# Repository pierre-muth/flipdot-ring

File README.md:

# flipdot-ring
Files of the flipdot-ring project
It's basically a big circular flipdot display acting as a clock.

Details on www.pierremuth.com

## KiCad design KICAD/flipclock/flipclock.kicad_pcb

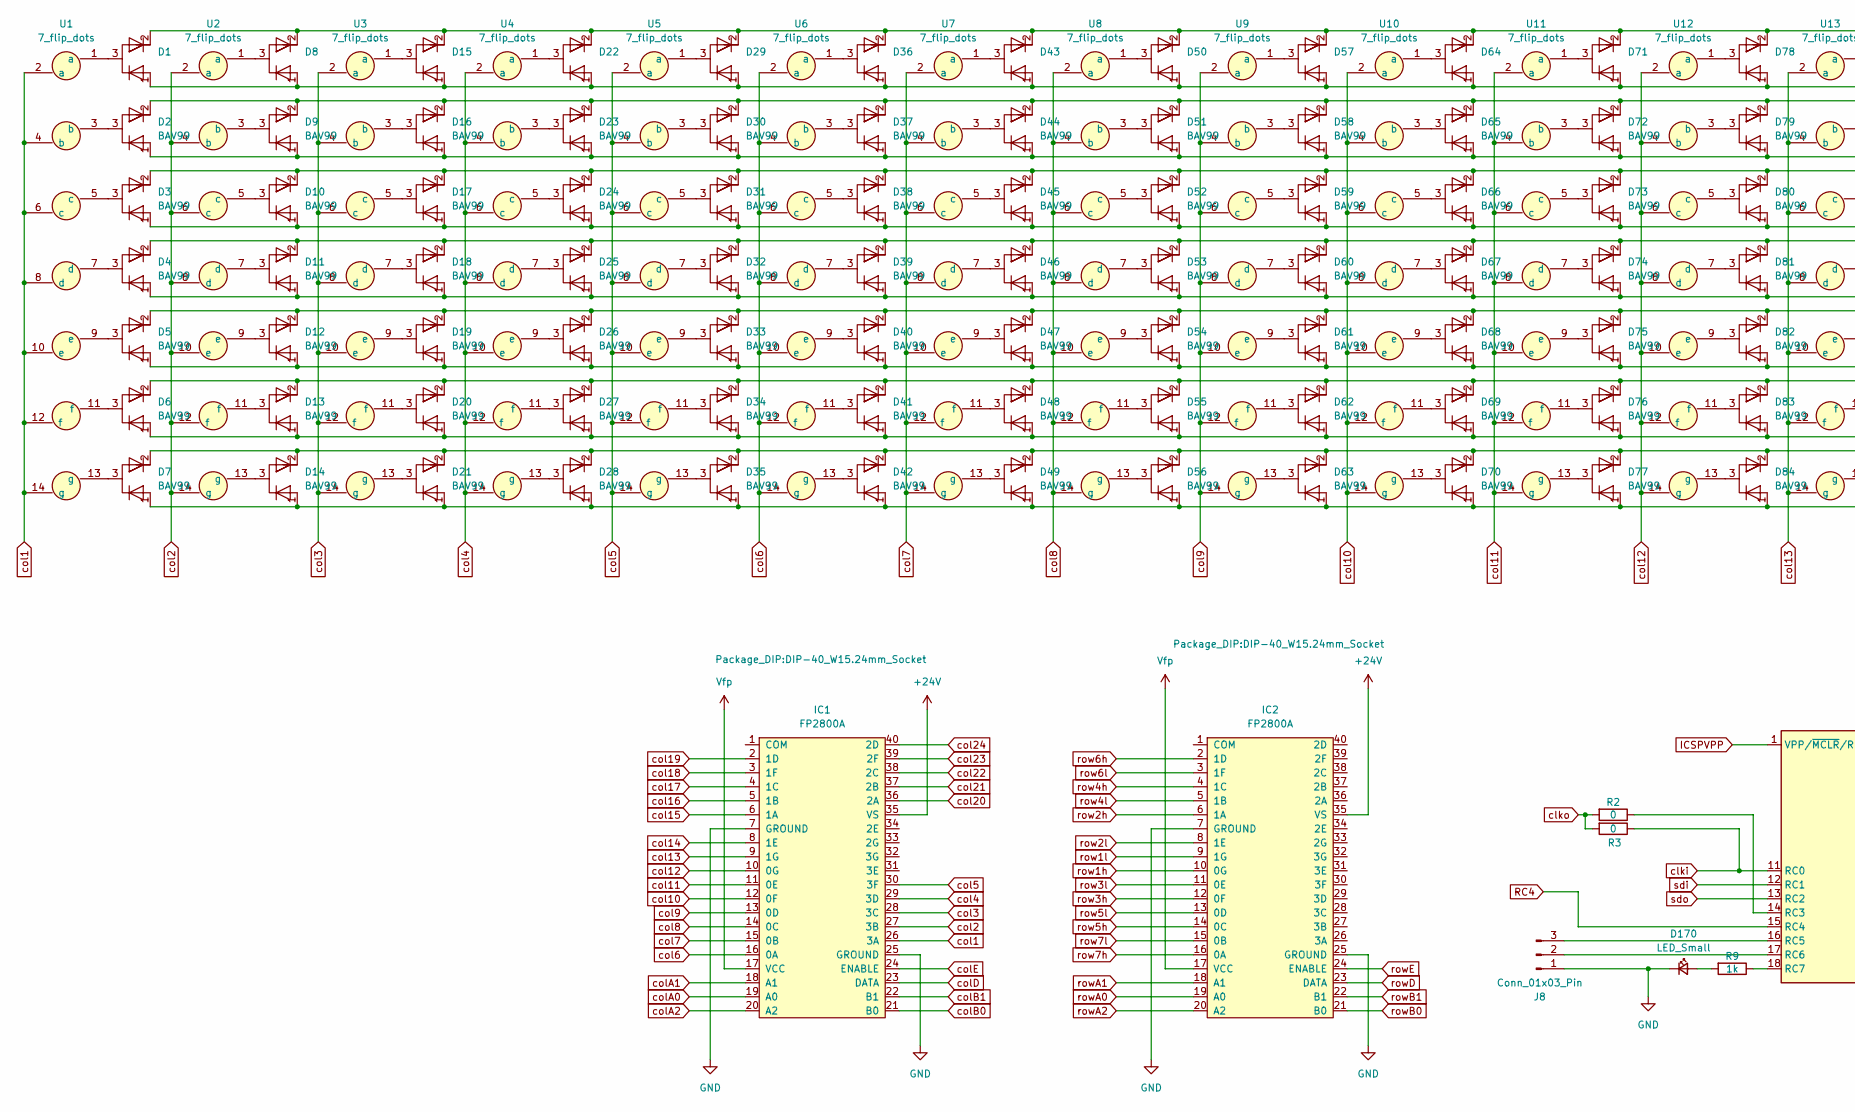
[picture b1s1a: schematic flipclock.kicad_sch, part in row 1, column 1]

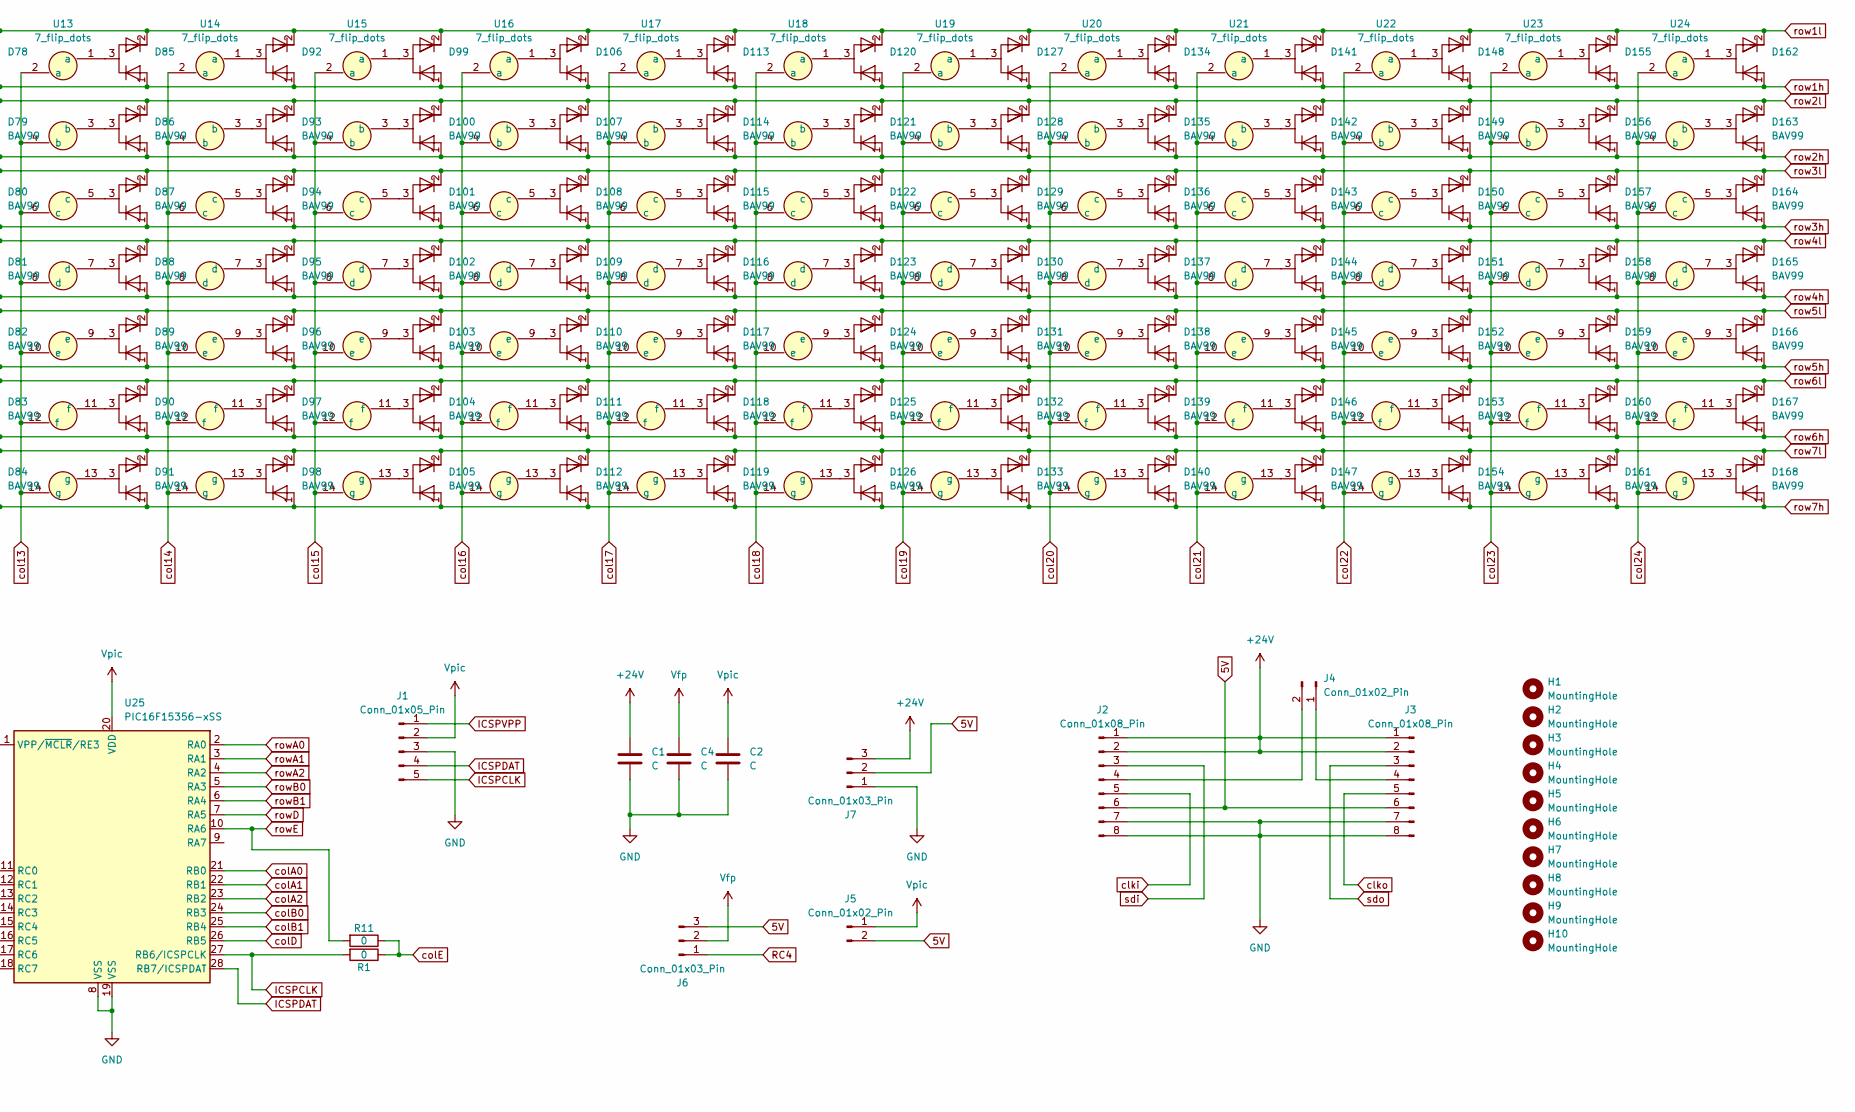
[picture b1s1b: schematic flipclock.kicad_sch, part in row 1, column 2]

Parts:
C1, C2, C4: C; C_1210_3225Metric_Pad1.33x2.70mm_HandSolder
D1, D2, D3, D4, D5, D6, D7, D8, D9, D10, D11, D12, D13, D14, D15, D16, D17, D18, D19, D20, D21, D22, D23, D24, D25, D26, D27, D28, D29, D30, D31, D32, D33, D34, D35, D36, D37, D38, D39, D40, D41, D42, D43, D44, D45, D46, D47, D48, D49, D50, D51, D52, D53, D54, D55, D56, D57, D58, D59, D60, D61, D62, D63, D64, D65, D66, D67, D68, D69, D70, D71, D72, D73, D74, D75, D76, D77, D78, D79, D80, D81, D82, D83, D84, D85, D86, D87, D88, D89, D90, D91, D92, D93, D94, D95, D96, D97, D98, D99, D100, D101, D102, D103, D104, D105, D106, D107, D108, D109, D110, D111, D112, D113, D114, D115, D116, D117, D118, D119, D120, D121, D122, D123, D124, D125, D126, D127, D128, D129, D130, D131, D132, D133, D134, D135, D136, D137, D138, D139, D140, D141, D142, D143, D144, D145, D146, D147, D148, D149, D150, D151, D152, D153, D154, D155, D156, D157, D158, D159, D160, D161, D162, D163, D164, D165, D166, D167, D168: BAV99; SOT-23
D170: LED_Small; LED_0805_2012Metric
H1, H2, H3, H4, H5, H6, H7, H8, H9, H10: MountingHole; MountingHole_3.2mm_M3
IC1, IC2: FP2800A; DIP-40_W15.24mm_Socket
J1: Conn_01x05_Pin; PinHeader_1x05_P2.54mm_Vertical
J2, J3: Conn_01x08_Pin; PinHeader_2x04_P2.54mm_Vertical
J4, J5: Conn_01x02_Pin; PinHeader_1x02_P2.54mm_Vertical
J6, J7, J8: Conn_01x03_Pin; PinHeader_1x03_P2.54mm_Vertical
R1, R2, R3, R11: 0; R_0805_2012Metric
R9: 1k; R_0805_2012Metric
U1, U2, U3, U4, U5, U6, U7, U8, U9, U10, U11, U12, U13, U14, U15, U16, U17, U18, U19, U20, U21, U22, U23, U24: 7_flip_dots; 7x1flipdot
U25: PIC16F15356-xSS; SSOP-28_5.3x10.2mm_P0.65mm

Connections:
5V: J2.6, J3.6, J5.2, J6.3, J7.2
+24V: C1.2, IC1.35 (VS), IC2.35 (VS), J2.1, J2.2, J3.1, J3.2, J7.3
GND: C1.1, C2.1, C4.1, D170.1 (K), IC1.7 (GROUND), IC1.25 (GROUND), IC2.7 (GROUND), IC2.25 (GROUND), J1.3, J2.7, J2.8, J3.7, J3.8, J7.1, J8.1, U25.8 (VSS), U25.19 (VSS)
ICSPCLK: J1.5, R1.2, U25.27 (RB6/ICSPCLK)
ICSPDAT: J1.4, U25.28 (RB7/ICSPDAT)
ICSPVPP: J1.1, U25.1 (VPP/~MCLR/RE3)
unnamed: D1.3 (K), U1.1 (a)
unnamed: D2.3 (K), U1.3 (b)
unnamed: D3.3 (K), U1.5 (c)
unnamed: D4.3 (K), U1.7 (d)
unnamed: D5.3 (K), U1.9 (e)
unnamed: D6.3 (K), U1.11 (f)
unnamed: D7.3 (K), U1.13 (g)
unnamed: D8.3 (K), U2.1 (a)
unnamed: D9.3 (K), U2.3 (b)
unnamed: D10.3 (K), U2.5 (c)
unnamed: D11.3 (K), U2.7 (d)
unnamed: D12.3 (K), U2.9 (e)
unnamed: D13.3 (K), U2.11 (f)
unnamed: D14.3 (K), U2.13 (g)
unnamed: D15.3 (K), U3.1 (a)
unnamed: D16.3 (K), U3.3 (b)
unnamed: D17.3 (K), U3.5 (c)
unnamed: D18.3 (K), U3.7 (d)
unnamed: D19.3 (K), U3.9 (e)
unnamed: D20.3 (K), U3.11 (f)
unnamed: D21.3 (K), U3.13 (g)
unnamed: D22.3 (K), U4.1 (a)
unnamed: D23.3 (K), U4.3 (b)
unnamed: D24.3 (K), U4.5 (c)
unnamed: D25.3 (K), U4.7 (d)
unnamed: D26.3 (K), U4.9 (e)
unnamed: D27.3 (K), U4.11 (f)
unnamed: D28.3 (K), U4.13 (g)
unnamed: D29.3 (K), U5.1 (a)
unnamed: D30.3 (K), U5.3 (b)
unnamed: D31.3 (K), U5.5 (c)
unnamed: D32.3 (K), U5.7 (d)
unnamed: D33.3 (K), U5.9 (e)
unnamed: D34.3 (K), U5.11 (f)
unnamed: D35.3 (K), U5.13 (g)
unnamed: D36.3 (K), U6.1 (a)
unnamed: D37.3 (K), U6.3 (b)
unnamed: D38.3 (K), U6.5 (c)
unnamed: D39.3 (K), U6.7 (d)
unnamed: D40.3 (K), U6.9 (e)
unnamed: D41.3 (K), U6.11 (f)
unnamed: D42.3 (K), U6.13 (g)
unnamed: D43.3 (K), U7.1 (a)
unnamed: D44.3 (K), U7.3 (b)
unnamed: D45.3 (K), U7.5 (c)
unnamed: D46.3 (K), U7.7 (d)
unnamed: D47.3 (K), U7.9 (e)
unnamed: D48.3 (K), U7.11 (f)
unnamed: D49.3 (K), U7.13 (g)
unnamed: D50.3 (K), U8.1 (a)
unnamed: D51.3 (K), U8.3 (b)
unnamed: D52.3 (K), U8.5 (c)
unnamed: D53.3 (K), U8.7 (d)
unnamed: D54.3 (K), U8.9 (e)
unnamed: D55.3 (K), U8.11 (f)
unnamed: D56.3 (K), U8.13 (g)
unnamed: D57.3 (K), U9.1 (a)
unnamed: D58.3 (K), U9.3 (b)
unnamed: D59.3 (K), U9.5 (c)
unnamed: D60.3 (K), U9.7 (d)
unnamed: D61.3 (K), U9.9 (e)
unnamed: D62.3 (K), U9.11 (f)
unnamed: D63.3 (K), U9.13 (g)
unnamed: D64.3 (K), U10.1 (a)
unnamed: D65.3 (K), U10.3 (b)
unnamed: D66.3 (K), U10.5 (c)
unnamed: D67.3 (K), U10.7 (d)
unnamed: D68.3 (K), U10.9 (e)
unnamed: D69.3 (K), U10.11 (f)
unnamed: D70.3 (K), U10.13 (g)
unnamed: D71.3 (K), U11.1 (a)
unnamed: D72.3 (K), U11.3 (b)
unnamed: D73.3 (K), U11.5 (c)
unnamed: D74.3 (K), U11.7 (d)
unnamed: D75.3 (K), U11.9 (e)
unnamed: D76.3 (K), U11.11 (f)
unnamed: D77.3 (K), U11.13 (g)
unnamed: D78.3 (K), U12.1 (a)
unnamed: D79.3 (K), U12.3 (b)
unnamed: D80.3 (K), U12.5 (c)
unnamed: D81.3 (K), U12.7 (d)
unnamed: D82.3 (K), U12.9 (e)
unnamed: D83.3 (K), U12.11 (f)
unnamed: D84.3 (K), U12.13 (g)
unnamed: D85.3 (K), U13.1 (a)
unnamed: D86.3 (K), U13.3 (b)
unnamed: D87.3 (K), U13.5 (c)
unnamed: D88.3 (K), U13.7 (d)
unnamed: D89.3 (K), U13.9 (e)
unnamed: D90.3 (K), U13.11 (f)
unnamed: D91.3 (K), U13.13 (g)
unnamed: D92.3 (K), U14.1 (a)
unnamed: D93.3 (K), U14.3 (b)
unnamed: D94.3 (K), U14.5 (c)
unnamed: D95.3 (K), U14.7 (d)
unnamed: D96.3 (K), U14.9 (e)
unnamed: D97.3 (K), U14.11 (f)
unnamed: D98.3 (K), U14.13 (g)
unnamed: D99.3 (K), U15.1 (a)
unnamed: D100.3 (K), U15.3 (b)
unnamed: D101.3 (K), U15.5 (c)
unnamed: D102.3 (K), U15.7 (d)
unnamed: D103.3 (K), U15.9 (e)
unnamed: D104.3 (K), U15.11 (f)
unnamed: D105.3 (K), U15.13 (g)
unnamed: D106.3 (K), U16.1 (a)
unnamed: D107.3 (K), U16.3 (b)
unnamed: D108.3 (K), U16.5 (c)
unnamed: D109.3 (K), U16.7 (d)
unnamed: D110.3 (K), U16.9 (e)
unnamed: D111.3 (K), U16.11 (f)
unnamed: D112.3 (K), U16.13 (g)
unnamed: D113.3 (K), U17.1 (a)
unnamed: D114.3 (K), U17.3 (b)
unnamed: D115.3 (K), U17.5 (c)
unnamed: D116.3 (K), U17.7 (d)
unnamed: D117.3 (K), U17.9 (e)
unnamed: D118.3 (K), U17.11 (f)
unnamed: D119.3 (K), U17.13 (g)
unnamed: D120.3 (K), U18.1 (a)
unnamed: D121.3 (K), U18.3 (b)
unnamed: D122.3 (K), U18.5 (c)
unnamed: D123.3 (K), U18.7 (d)
unnamed: D124.3 (K), U18.9 (e)
unnamed: D125.3 (K), U18.11 (f)
unnamed: D126.3 (K), U18.13 (g)
unnamed: D127.3 (K), U19.1 (a)
unnamed: D128.3 (K), U19.3 (b)
unnamed: D129.3 (K), U19.5 (c)
unnamed: D130.3 (K), U19.7 (d)
unnamed: D131.3 (K), U19.9 (e)
unnamed: D132.3 (K), U19.11 (f)
unnamed: D133.3 (K), U19.13 (g)
unnamed: D134.3 (K), U20.1 (a)
unnamed: D135.3 (K), U20.3 (b)
unnamed: D136.3 (K), U20.5 (c)
unnamed: D137.3 (K), U20.7 (d)
unnamed: D138.3 (K), U20.9 (e)
unnamed: D139.3 (K), U20.11 (f)
unnamed: D140.3 (K), U20.13 (g)
unnamed: D141.3 (K), U21.1 (a)
unnamed: D142.3 (K), U21.3 (b)
unnamed: D143.3 (K), U21.5 (c)
unnamed: D144.3 (K), U21.7 (d)
unnamed: D145.3 (K), U21.9 (e)
unnamed: D146.3 (K), U21.11 (f)
unnamed: D147.3 (K), U21.13 (g)
unnamed: D148.3 (K), U22.1 (a)
unnamed: D149.3 (K), U22.3 (b)
unnamed: D150.3 (K), U22.5 (c)
unnamed: D151.3 (K), U22.7 (d)
unnamed: D152.3 (K), U22.9 (e)
unnamed: D153.3 (K), U22.11 (f)
unnamed: D154.3 (K), U22.13 (g)
unnamed: D155.3 (K), U23.1 (a)
unnamed: D156.3 (K), U23.3 (b)
unnamed: D157.3 (K), U23.5 (c)
unnamed: D158.3 (K), U23.7 (d)
unnamed: D159.3 (K), U23.9 (e)
unnamed: D160.3 (K), U23.11 (f)
unnamed: D161.3 (K), U23.13 (g)
unnamed: D162.3 (K), U24.1 (a)
unnamed: D163.3 (K), U24.3 (b)
unnamed: D164.3 (K), U24.5 (c)
unnamed: D165.3 (K), U24.7 (d)
unnamed: D166.3 (K), U24.9 (e)
unnamed: D167.3 (K), U24.11 (f)
unnamed: D168.3 (K), U24.13 (g)
unnamed: D170.2 (A), R9.2
unnamed: J2.4, J4.2
unnamed: J3.4, J4.1
unnamed: J8.2, U25.17 (RC6)
unnamed: J8.3, U25.16 (RC5)
unnamed: R2.1, U25.14 (RC3)
unnamed: R9.1, U25.18 (RC7)
RC4: J6.1, U25.15 (RC4)
Vfp: C4.2, IC1.17 (VCC), IC2.17 (VCC), J6.2
Vpic: C2.2, J1.2, J5.1, U25.20 (VDD)
clki: J2.5, R3.1, U25.11 (RC0)
clko: J3.5, R2.2, R3.2
col1: IC1.26 (3A), U1.2 (a), U1.4 (b), U1.6 (c), U1.8 (d), U1.10 (e), U1.12 (f), U1.14 (g)
col2: IC1.27 (3B), U2.2 (a), U2.4 (b), U2.6 (c), U2.8 (d), U2.10 (e), U2.12 (f), U2.14 (g)
col3: IC1.28 (3C), U3.2 (a), U3.4 (b), U3.6 (c), U3.8 (d), U3.10 (e), U3.12 (f), U3.14 (g)
col4: IC1.29 (3D), U4.2 (a), U4.4 (b), U4.6 (c), U4.8 (d), U4.10 (e), U4.12 (f), U4.14 (g)
col5: IC1.30 (3F), U5.2 (a), U5.4 (b), U5.6 (c), U5.8 (d), U5.10 (e), U5.12 (f), U5.14 (g)
col6: IC1.16 (0A), U6.2 (a), U6.4 (b), U6.6 (c), U6.8 (d), U6.10 (e), U6.12 (f), U6.14 (g)
col7: IC1.15 (0B), U7.2 (a), U7.4 (b), U7.6 (c), U7.8 (d), U7.10 (e), U7.12 (f), U7.14 (g)
col8: IC1.14 (0C), U8.2 (a), U8.4 (b), U8.6 (c), U8.8 (d), U8.10 (e), U8.12 (f), U8.14 (g)
col9: IC1.13 (0D), U9.2 (a), U9.4 (b), U9.6 (c), U9.8 (d), U9.10 (e), U9.12 (f), U9.14 (g)
col10: IC1.12 (0F), U10.2 (a), U10.4 (b), U10.6 (c), U10.8 (d), U10.10 (e), U10.12 (f), U10.14 (g)
col11: IC1.11 (0E), U11.2 (a), U11.4 (b), U11.6 (c), U11.8 (d), U11.10 (e), U11.12 (f), U11.14 (g)
col12: IC1.10 (0G), U12.2 (a), U12.4 (b), U12.6 (c), U12.8 (d), U12.10 (e), U12.12 (f), U12.14 (g)
col13: IC1.9 (1G), U13.2 (a), U13.4 (b), U13.6 (c), U13.8 (d), U13.10 (e), U13.12 (f), U13.14 (g)
col14: IC1.8 (1E), U14.2 (a), U14.4 (b), U14.6 (c), U14.8 (d), U14.10 (e), U14.12 (f), U14.14 (g)
col15: IC1.6 (1A), U15.2 (a), U15.4 (b), U15.6 (c), U15.8 (d), U15.10 (e), U15.12 (f), U15.14 (g)
col16: IC1.5 (1B), U16.2 (a), U16.4 (b), U16.6 (c), U16.8 (d), U16.10 (e), U16.12 (f), U16.14 (g)
col17: IC1.4 (1C), U17.2 (a), U17.4 (b), U17.6 (c), U17.8 (d), U17.10 (e), U17.12 (f), U17.14 (g)
col18: IC1.3 (1F), U18.2 (a), U18.4 (b), U18.6 (c), U18.8 (d), U18.10 (e), U18.12 (f), U18.14 (g)
col19: IC1.2 (1D), U19.2 (a), U19.4 (b), U19.6 (c), U19.8 (d), U19.10 (e), U19.12 (f), U19.14 (g)
col20: IC1.36 (2A), U20.2 (a), U20.4 (b), U20.6 (c), U20.8 (d), U20.10 (e), U20.12 (f), U20.14 (g)
col21: IC1.37 (2B), U21.2 (a), U21.4 (b), U21.6 (c), U21.8 (d), U21.10 (e), U21.12 (f), U21.14 (g)
col22: IC1.38 (2C), U22.2 (a), U22.4 (b), U22.6 (c), U22.8 (d), U22.10 (e), U22.12 (f), U22.14 (g)
col23: IC1.39 (2F), U23.2 (a), U23.4 (b), U23.6 (c), U23.8 (d), U23.10 (e), U23.12 (f), U23.14 (g)
col24: IC1.40 (2D), U24.2 (a), U24.4 (b), U24.6 (c), U24.8 (d), U24.10 (e), U24.12 (f), U24.14 (g)
colA0: IC1.19 (A0), U25.21 (RB0)
colA1: IC1.18 (A1), U25.22 (RB1)
colA2: IC1.20 (A2), U25.23 (RB2)
colB0: IC1.21 (B0), U25.24 (RB3)
colB1: IC1.22 (B1), U25.25 (RB4)
colD: IC1.23 (DATA), U25.26 (RB5)
colE: IC1.24 (ENABLE), R1.1, R11.1
row1h: D1.1 (K), D8.1 (K), D15.1 (K), D22.1 (K), D29.1 (K), D36.1 (K), D43.1 (K), D50.1 (K), D57.1 (K), D64.1 (K), D71.1 (K), D78.1 (K), D85.1 (K), D92.1 (K), D99.1 (K), D106.1 (K), D113.1 (K), D120.1 (K), D127.1 (K), D134.1 (K), D141.1 (K), D148.1 (K), D155.1 (K), D162.1 (K), IC2.10 (0G)
row1l: D1.2 (A), D8.2 (A), D15.2 (A), D22.2 (A), D29.2 (A), D36.2 (A), D43.2 (A), D50.2 (A), D57.2 (A), D64.2 (A), D71.2 (A), D78.2 (A), D85.2 (A), D92.2 (A), D99.2 (A), D106.2 (A), D113.2 (A), D120.2 (A), D127.2 (A), D134.2 (A), D141.2 (A), D148.2 (A), D155.2 (A), D162.2 (A), IC2.9 (1G)
row2h: D2.1 (K), D9.1 (K), D16.1 (K), D23.1 (K), D30.1 (K), D37.1 (K), D44.1 (K), D51.1 (K), D58.1 (K), D65.1 (K), D72.1 (K), D79.1 (K), D86.1 (K), D93.1 (K), D100.1 (K), D107.1 (K), D114.1 (K), D121.1 (K), D128.1 (K), D135.1 (K), D142.1 (K), D149.1 (K), D156.1 (K), D163.1 (K), IC2.6 (1A)
row2l: D2.2 (A), D9.2 (A), D16.2 (A), D23.2 (A), D30.2 (A), D37.2 (A), D44.2 (A), D51.2 (A), D58.2 (A), D65.2 (A), D72.2 (A), D79.2 (A), D86.2 (A), D93.2 (A), D100.2 (A), D107.2 (A), D114.2 (A), D121.2 (A), D128.2 (A), D135.2 (A), D142.2 (A), D149.2 (A), D156.2 (A), D163.2 (A), IC2.8 (1E)
row3h: D3.1 (K), D10.1 (K), D17.1 (K), D24.1 (K), D31.1 (K), D38.1 (K), D45.1 (K), D52.1 (K), D59.1 (K), D66.1 (K), D73.1 (K), D80.1 (K), D87.1 (K), D94.1 (K), D101.1 (K), D108.1 (K), D115.1 (K), D122.1 (K), D129.1 (K), D136.1 (K), D143.1 (K), D150.1 (K), D157.1 (K), D164.1 (K), IC2.12 (0F)
row3l: D3.2 (A), D10.2 (A), D17.2 (A), D24.2 (A), D31.2 (A), D38.2 (A), D45.2 (A), D52.2 (A), D59.2 (A), D66.2 (A), D73.2 (A), D80.2 (A), D87.2 (A), D94.2 (A), D101.2 (A), D108.2 (A), D115.2 (A), D122.2 (A), D129.2 (A), D136.2 (A), D143.2 (A), D150.2 (A), D157.2 (A), D164.2 (A), IC2.11 (0E)
row4h: D4.1 (K), D11.1 (K), D18.1 (K), D25.1 (K), D32.1 (K), D39.1 (K), D46.1 (K), D53.1 (K), D60.1 (K), D67.1 (K), D74.1 (K), D81.1 (K), D88.1 (K), D95.1 (K), D102.1 (K), D109.1 (K), D116.1 (K), D123.1 (K), D130.1 (K), D137.1 (K), D144.1 (K), D151.1 (K), D158.1 (K), D165.1 (K), IC2.4 (1C)
row4l: D4.2 (A), D11.2 (A), D18.2 (A), D25.2 (A), D32.2 (A), D39.2 (A), D46.2 (A), D53.2 (A), D60.2 (A), D67.2 (A), D74.2 (A), D81.2 (A), D88.2 (A), D95.2 (A), D102.2 (A), D109.2 (A), D116.2 (A), D123.2 (A), D130.2 (A), D137.2 (A), D144.2 (A), D151.2 (A), D158.2 (A), D165.2 (A), IC2.5 (1B)
row5h: D5.1 (K), D12.1 (K), D19.1 (K), D26.1 (K), D33.1 (K), D40.1 (K), D47.1 (K), D54.1 (K), D61.1 (K), D68.1 (K), D75.1 (K), D82.1 (K), D89.1 (K), D96.1 (K), D103.1 (K), D110.1 (K), D117.1 (K), D124.1 (K), D131.1 (K), D138.1 (K), D145.1 (K), D152.1 (K), D159.1 (K), D166.1 (K), IC2.14 (0C)
row5l: D5.2 (A), D12.2 (A), D19.2 (A), D26.2 (A), D33.2 (A), D40.2 (A), D47.2 (A), D54.2 (A), D61.2 (A), D68.2 (A), D75.2 (A), D82.2 (A), D89.2 (A), D96.2 (A), D103.2 (A), D110.2 (A), D117.2 (A), D124.2 (A), D131.2 (A), D138.2 (A), D145.2 (A), D152.2 (A), D159.2 (A), D166.2 (A), IC2.13 (0D)
row6h: D6.1 (K), D13.1 (K), D20.1 (K), D27.1 (K), D34.1 (K), D41.1 (K), D48.1 (K), D55.1 (K), D62.1 (K), D69.1 (K), D76.1 (K), D83.1 (K), D90.1 (K), D97.1 (K), D104.1 (K), D111.1 (K), D118.1 (K), D125.1 (K), D132.1 (K), D139.1 (K), D146.1 (K), D153.1 (K), D160.1 (K), D167.1 (K), IC2.2 (1D)
row6l: D6.2 (A), D13.2 (A), D20.2 (A), D27.2 (A), D34.2 (A), D41.2 (A), D48.2 (A), D55.2 (A), D62.2 (A), D69.2 (A), D76.2 (A), D83.2 (A), D90.2 (A), D97.2 (A), D104.2 (A), D111.2 (A), D118.2 (A), D125.2 (A), D132.2 (A), D139.2 (A), D146.2 (A), D153.2 (A), D160.2 (A), D167.2 (A), IC2.3 (1F)
row7h: D7.1 (K), D14.1 (K), D21.1 (K), D28.1 (K), D35.1 (K), D42.1 (K), D49.1 (K), D56.1 (K), D63.1 (K), D70.1 (K), D77.1 (K), D84.1 (K), D91.1 (K), D98.1 (K), D105.1 (K), D112.1 (K), D119.1 (K), D126.1 (K), D133.1 (K), D140.1 (K), D147.1 (K), D154.1 (K), D161.1 (K), D168.1 (K), IC2.16 (0A)
row7l: D7.2 (A), D14.2 (A), D21.2 (A), D28.2 (A), D35.2 (A), D42.2 (A), D49.2 (A), D56.2 (A), D63.2 (A), D70.2 (A), D77.2 (A), D84.2 (A), D91.2 (A), D98.2 (A), D105.2 (A), D112.2 (A), D119.2 (A), D126.2 (A), D133.2 (A), D140.2 (A), D147.2 (A), D154.2 (A), D161.2 (A), D168.2 (A), IC2.15 (0B)
rowA0: IC2.19 (A0), U25.2 (RA0)
rowA1: IC2.18 (A1), U25.3 (RA1)
rowA2: IC2.20 (A2), U25.4 (RA2)
rowB0: IC2.21 (B0), U25.5 (RA3)
rowB1: IC2.22 (B1), U25.6 (RA4)
rowD: IC2.23 (DATA), U25.7 (RA5)
rowE: IC2.24 (ENABLE), R11.2, U25.10 (RA6)
sdi: J2.3, U25.12 (RC1)
sdo: J3.3, U25.13 (RC2)

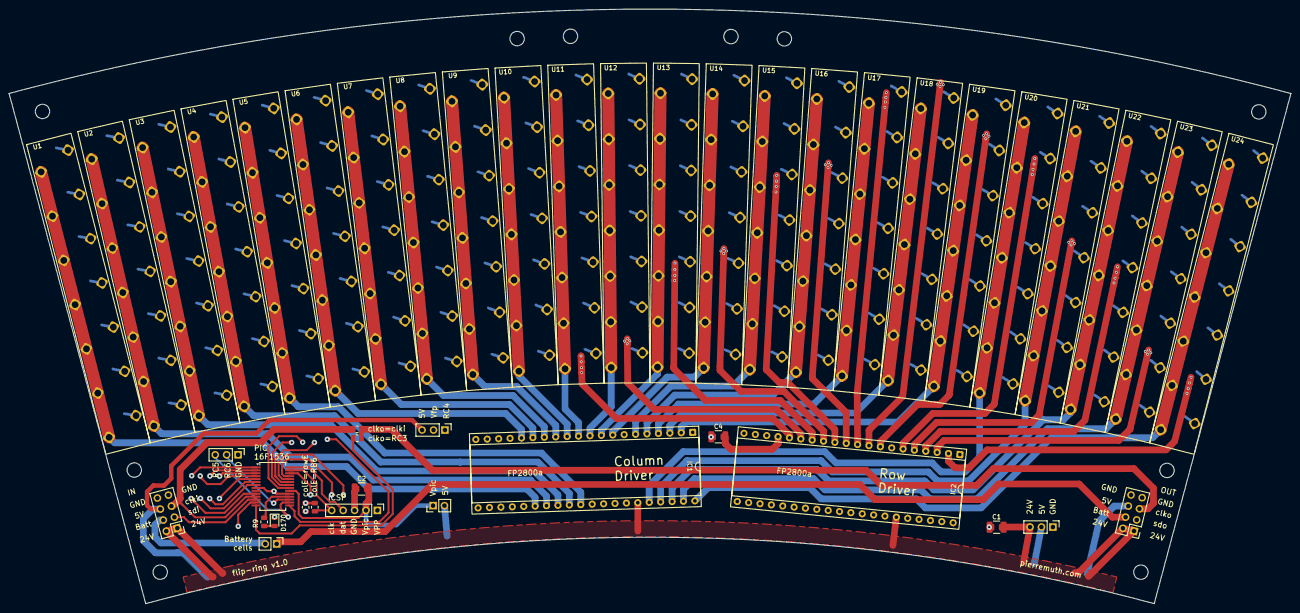
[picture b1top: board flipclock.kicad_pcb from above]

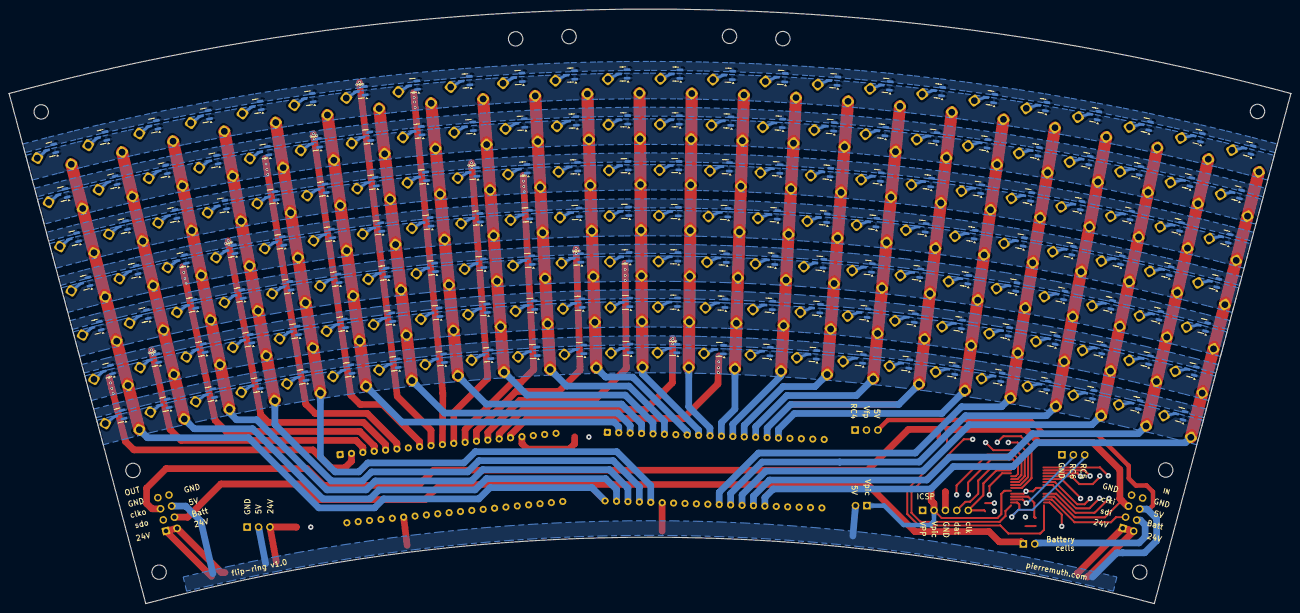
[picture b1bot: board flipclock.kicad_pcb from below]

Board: 4 copper layers, 285.2 x 132.3 mm, 222 parts (168 on the bottom side), 240 nets.

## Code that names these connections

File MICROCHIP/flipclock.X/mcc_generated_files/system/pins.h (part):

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// get/set IO_RA0 aliases
#define rowA0_TRIS                 TRISAbits.TRISA0
#define rowA0_LAT                  LATAbits.LATA0
#define rowA0_PORT                 PORTAbits.RA0
#define rowA0_WPU                  WPUAbits.WPUA0
#define rowA0_OD                   ODCONAbits.ODCA0
#define rowA0_ANS                  ANSELAbits.ANSA0
#define rowA0_SetHigh()            do { LATAbits.LATA0 = 1; } while(0)
#define rowA0_SetLow()             do { LATAbits.LATA0 = 0; } while(0)
#define rowA0_Toggle()             do { LATAbits.LATA0 = ~LATAbits.LATA0; } while(0)
#define rowA0_GetValue()           PORTAbits.RA0
#define rowA0_SetDigitalInput()    do { TRISAbits.TRISA0 = 1; } while(0)
#define rowA0_SetDigitalOutput()   do { TRISAbits.TRISA0 = 0; } while(0)
#define rowA0_SetPullup()          do { WPUAbits.WPUA0 = 1; } while(0)
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// get/set IO_RA1 aliases
#define rowA1_TRIS                 TRISAbits.TRISA1
#define rowA1_LAT                  LATAbits.LATA1
#define rowA1_PORT                 PORTAbits.RA1
#define rowA1_WPU                  WPUAbits.WPUA1
#define rowA1_OD                   ODCONAbits.ODCA1
#define rowA1_ANS                  ANSELAbits.ANSA1
#define rowA1_SetHigh()            do { LATAbits.LATA1 = 1; } while(0)
#define rowA1_SetLow()             do { LATAbits.LATA1 = 0; } while(0)
#define rowA1_Toggle()             do { LATAbits.LATA1 = ~LATAbits.LATA1; } while(0)
#define rowA1_GetValue()           PORTAbits.RA1
#define rowA1_SetDigitalInput()    do { TRISAbits.TRISA1 = 1; } while(0)
#define rowA1_SetDigitalOutput()   do { TRISAbits.TRISA1 = 0; } while(0)
#define rowA1_SetPullup()          do { WPUAbits.WPUA1 = 1; } while(0)
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// get/set IO_RA2 aliases
#define rowA2_TRIS                 TRISAbits.TRISA2
#define rowA2_LAT                  LATAbits.LATA2
#define rowA2_PORT                 PORTAbits.RA2
#define rowA2_WPU                  WPUAbits.WPUA2
#define rowA2_OD                   ODCONAbits.ODCA2
#define rowA2_ANS                  ANSELAbits.ANSA2
#define rowA2_SetHigh()            do { LATAbits.LATA2 = 1; } while(0)
#define rowA2_SetLow()             do { LATAbits.LATA2 = 0; } while(0)
#define rowA2_Toggle()             do { LATAbits.LATA2 = ~LATAbits.LATA2; } while(0)
#define rowA2_GetValue()           PORTAbits.RA2
#define rowA2_SetDigitalInput()    do { TRISAbits.TRISA2 = 1; } while(0)
#define rowA2_SetDigitalOutput()   do { TRISAbits.TRISA2 = 0; } while(0)
#define rowA2_SetPullup()          do { WPUAbits.WPUA2 = 1; } while(0)
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// get/set IO_RA3 aliases
#define rowB0_TRIS                 TRISAbits.TRISA3
#define rowB0_LAT                  LATAbits.LATA3
#define rowB0_PORT                 PORTAbits.RA3
#define rowB0_WPU                  WPUAbits.WPUA3
#define rowB0_OD                   ODCONAbits.ODCA3
#define rowB0_ANS                  ANSELAbits.ANSA3
#define rowB0_SetHigh()            do { LATAbits.LATA3 = 1; } while(0)
#define rowB0_SetLow()             do { LATAbits.LATA3 = 0; } while(0)
#define rowB0_Toggle()             do { LATAbits.LATA3 = ~LATAbits.LATA3; } while(0)
#define rowB0_GetValue()           PORTAbits.RA3
#define rowB0_SetDigitalInput()    do { TRISAbits.TRISA3 = 1; } while(0)
#define rowB0_SetDigitalOutput()   do { TRISAbits.TRISA3 = 0; } while(0)
#define rowB0_SetPullup()          do { WPUAbits.WPUA3 = 1; } while(0)
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// get/set IO_RA4 aliases
#define rowB1_TRIS                 TRISAbits.TRISA4
#define rowB1_LAT                  LATAbits.LATA4
#define rowB1_PORT                 PORTAbits.RA4
#define rowB1_WPU                  WPUAbits.WPUA4
#define rowB1_OD                   ODCONAbits.ODCA4
#define rowB1_ANS                  ANSELAbits.ANSA4
#define rowB1_SetHigh()            do { LATAbits.LATA4 = 1; } while(0)
#define rowB1_SetLow()             do { LATAbits.LATA4 = 0; } while(0)
#define rowB1_Toggle()             do { LATAbits.LATA4 = ~LATAbits.LATA4; } while(0)
#define rowB1_GetValue()           PORTAbits.RA4
#define rowB1_SetDigitalInput()    do { TRISAbits.TRISA4 = 1; } while(0)
#define rowB1_SetDigitalOutput()   do { TRISAbits.TRISA4 = 0; } while(0)
#define rowB1_SetPullup()          do { WPUAbits.WPUA4 = 1; } while(0)
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// get/set IO_RA5 aliases
#define rowD_TRIS                 TRISAbits.TRISA5
#define rowD_LAT                  LATAbits.LATA5
#define rowD_PORT                 PORTAbits.RA5
#define rowD_WPU                  WPUAbits.WPUA5
#define rowD_OD                   ODCONAbits.ODCA5
#define rowD_ANS                  ANSELAbits.ANSA5
#define rowD_SetHigh()            do { LATAbits.LATA5 = 1; } while(0)
#define rowD_SetLow()             do { LATAbits.LATA5 = 0; } while(0)
#define rowD_Toggle()             do { LATAbits.LATA5 = ~LATAbits.LATA5; } while(0)
#define rowD_GetValue()           PORTAbits.RA5
#define rowD_SetDigitalInput()    do { TRISAbits.TRISA5 = 1; } while(0)
#define rowD_SetDigitalOutput()   do { TRISAbits.TRISA5 = 0; } while(0)
#define rowD_SetPullup()          do { WPUAbits.WPUA5 = 1; } while(0)
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// get/set IO_RA6 aliases
#define rowE_TRIS                 TRISAbits.TRISA6
#define rowE_LAT                  LATAbits.LATA6
#define rowE_PORT                 PORTAbits.RA6
#define rowE_WPU                  WPUAbits.WPUA6
#define rowE_OD                   ODCONAbits.ODCA6
#define rowE_ANS                  ANSELAbits.ANSA6
#define rowE_SetHigh()            do { LATAbits.LATA6 = 1; } while(0)
#define rowE_SetLow()             do { LATAbits.LATA6 = 0; } while(0)
#define rowE_Toggle()             do { LATAbits.LATA6 = ~LATAbits.LATA6; } while(0)
#define rowE_GetValue()           PORTAbits.RA6
#define rowE_SetDigitalInput()    do { TRISAbits.TRISA6 = 1; } while(0)
#define rowE_SetDigitalOutput()   do { TRISAbits.TRISA6 = 0; } while(0)
#define rowE_SetPullup()          do { WPUAbits.WPUA6 = 1; } while(0)
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// get/set IO_RB0 aliases
#define colA0_TRIS                 TRISBbits.TRISB0
#define colA0_LAT                  LATBbits.LATB0
#define colA0_PORT                 PORTBbits.RB0
#define colA0_WPU                  WPUBbits.WPUB0
#define colA0_OD                   ODCONBbits.ODCB0
#define colA0_ANS                  ANSELBbits.ANSB0
#define colA0_SetHigh()            do { LATBbits.LATB0 = 1; } while(0)
#define colA0_SetLow()             do { LATBbits.LATB0 = 0; } while(0)
#define colA0_Toggle()             do { LATBbits.LATB0 = ~LATBbits.LATB0; } while(0)
#define colA0_GetValue()           PORTBbits.RB0
#define colA0_SetDigitalInput()    do { TRISBbits.TRISB0 = 1; } while(0)
#define colA0_SetDigitalOutput()   do { TRISBbits.TRISB0 = 0; } while(0)
#define colA0_SetPullup()          do { WPUBbits.WPUB0 = 1; } while(0)
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// get/set IO_RB1 aliases
#define colA1_TRIS                 TRISBbits.TRISB1
#define colA1_LAT                  LATBbits.LATB1
#define colA1_PORT                 PORTBbits.RB1
#define colA1_WPU                  WPUBbits.WPUB1
#define colA1_OD                   ODCONBbits.ODCB1
#define colA1_ANS                  ANSELBbits.ANSB1
#define colA1_SetHigh()            do { LATBbits.LATB1 = 1; } while(0)
#define colA1_SetLow()             do { LATBbits.LATB1 = 0; } while(0)
#define colA1_Toggle()             do { LATBbits.LATB1 = ~LATBbits.LATB1; } while(0)
#define colA1_GetValue()           PORTBbits.RB1
#define colA1_SetDigitalInput()    do { TRISBbits.TRISB1 = 1; } while(0)
#define colA1_SetDigitalOutput()   do { TRISBbits.TRISB1 = 0; } while(0)
#define colA1_SetPullup()          do { WPUBbits.WPUB1 = 1; } while(0)
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// get/set IO_RB2 aliases
#define colA2_TRIS                 TRISBbits.TRISB2
#define colA2_LAT                  LATBbits.LATB2
#define colA2_PORT                 PORTBbits.RB2
#define colA2_WPU                  WPUBbits.WPUB2
#define colA2_OD                   ODCONBbits.ODCB2
#define colA2_ANS                  ANSELBbits.ANSB2
#define colA2_SetHigh()            do { LATBbits.LATB2 = 1; } while(0)
#define colA2_SetLow()             do { LATBbits.LATB2 = 0; } while(0)
#define colA2_Toggle()             do { LATBbits.LATB2 = ~LATBbits.LATB2; } while(0)
#define colA2_GetValue()           PORTBbits.RB2
#define colA2_SetDigitalInput()    do { TRISBbits.TRISB2 = 1; } while(0)
#define colA2_SetDigitalOutput()   do { TRISBbits.TRISB2 = 0; } while(0)
#define colA2_SetPullup()          do { WPUBbits.WPUB2 = 1; } while(0)
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// get/set IO_RB3 aliases
#define colB0_TRIS                 TRISBbits.TRISB3
#define colB0_LAT                  LATBbits.LATB3
#define colB0_PORT                 PORTBbits.RB3
#define colB0_WPU                  WPUBbits.WPUB3
#define colB0_OD                   ODCONBbits.ODCB3
#define colB0_ANS                  ANSELBbits.ANSB3
#define colB0_SetHigh()            do { LATBbits.LATB3 = 1; } while(0)
#define colB0_SetLow()             do { LATBbits.LATB3 = 0; } while(0)
#define colB0_Toggle()             do { LATBbits.LATB3 = ~LATBbits.LATB3; } while(0)
#define colB0_GetValue()           PORTBbits.RB3
#define colB0_SetDigitalInput()    do { TRISBbits.TRISB3 = 1; } while(0)
#define colB0_SetDigitalOutput()   do { TRISBbits.TRISB3 = 0; } while(0)
#define colB0_SetPullup()          do { WPUBbits.WPUB3 = 1; } while(0)
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
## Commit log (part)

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2026-02-03 Update comments
2026-02-25 Restore includes and configuration logic in main.cpp
2026-02-27 edited todo list
2026-02-27 update todo list
2026-03-01 PIC in sleep mode after display refreshing
2026-03-01 todo list update
2026-03-02 Create TODO.txt for project planning
    Added a TODO list for project tasks and features.
2026-03-02 move TODO list
2026-03-02 add todo list
2026-03-02 Add setting custom time
2026-03-09 Mark tasks as done and add new details
    Updated tasks with completion status and additional notes.
2026-03-11 more check of incoming data
2026-03-11 set latching time to 5ms
2026-03-13 Update todo.txt with completed tasks and notes
    Added completed tasks for voltage divider and PIC/ESP32 code updates.
2026-03-15 ADC for main battery and Wakeup button
2026-03-16 add demo mode
2026-03-16 Add java simulator
2026-03-17 Refactor todo items for clarity and updates
2026-03-19 Clarify night time configuration in todo.txt
2026-03-19 update draft
2026-03-23 Enhance README with project description and details
    Added a brief description and details about the project.
2026-03-23 Enhance README with image and video links
    Added a screenshot and a YouTube video link to the README.
2026-03-23 Remove flipdot-ring image from README
    Removed image of flipdot-ring from README.

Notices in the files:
MICROCHIP/flipclock.X/mcc_generated_files/system/pins.h:
© [2026] Microchip Technology Inc. and its subsidiaries.
